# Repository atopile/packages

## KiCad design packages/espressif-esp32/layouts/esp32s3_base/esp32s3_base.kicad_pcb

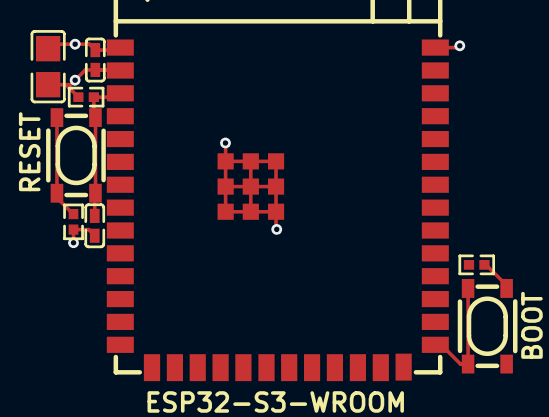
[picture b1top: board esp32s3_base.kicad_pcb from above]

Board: 2 copper layers, 9 parts (0 on the bottom side), 6 nets.

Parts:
C1: 100nF ±10% 16V X7R; C0402
C2: 22µF ±20% 25V X5R; C0805
C3: 1µF ±10% 25V X5R; C0402
R1, R3: 100Ω ±1% 62.5mW; R0402
R2: 10kΩ ±1% 62.5mW; R0402
SW1, SW2: KEY-SMD_4P-L4.2-W3.2-P2.20-LS4.6
U1: WIRELM-SMD_ESP32-S3-WROOM-1

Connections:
EN: C3.1, R2.1, SW2.1, SW2.2, U1.3
gnd: C1.2, C2.2, C3.2, R1.2, R3.2, U1.1, U1.40, U1.41
hv: C1.1, C2.1, R2.2, U1.2
line: SW1.1, SW1.2, U1.27
unnamed[1]: R3.1, SW2.3, SW2.4
unnamed[1]-1: R1.1, SW1.3, SW1.4

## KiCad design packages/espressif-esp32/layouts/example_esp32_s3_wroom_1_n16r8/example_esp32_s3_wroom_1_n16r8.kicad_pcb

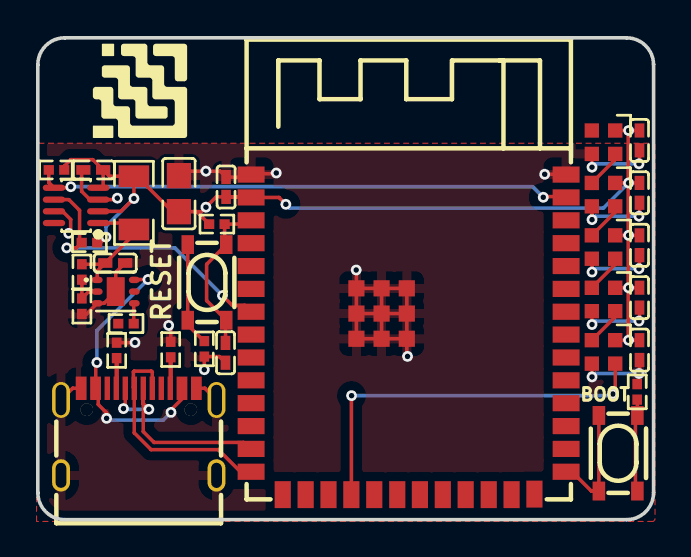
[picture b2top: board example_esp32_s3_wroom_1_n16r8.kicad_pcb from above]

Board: 2 copper layers, 34.2 x 26.8 mm, 32 parts (0 on the bottom side), 21 nets.

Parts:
C1, C2, C3, C4, C6, C7, C8: 100nF ±10% 16V X7R; C0402
C5, C10: 1µF ±10% 25V X5R; C0402
C9: 22µF ±20% 25V X5R; C0805
LED1, LED2, LED3, LED4, LED5: LED-SMD_4P-L2.0-W2.0-BR
R1: 180mΩ ±5% 250mW; R1206
R2, R4: 100Ω ±1% 62.5mW; R0402
R3, R5, R7: 10kΩ ±1% 62.5mW; R0402
R6: 2kΩ ±1% 62.5mW; R0402
R8, R9, R10, R11: 4.7kΩ ±1% 62.5mW; R0402
SW1, SW2: KEY-SMD_4P-L4.2-W3.2-P2.20-LS4.6
U1: SOT-23-8_L2.9-W1.6-P0.65-LS2.8-BR
U2: WIRELM-SMD_ESP32-S3-WROOM-1
U3: WSON-6_L2.0-W2.0-P0.65-TL-EP
USB1: USB-C-SMD_KH-TYPE-C-16P

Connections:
A5: R10.1, USB1.A5
B5: R11.1, USB1.B5
DIN: LED1.4, U2.18
DOUT: LED1.2, LED2.4
DOUT-1: LED2.2, LED3.4
DOUT-2: LED3.2, LED4.4
DOUT-3: LED4.2, LED5.4
EN: C10.1, R3.1, SW2.1, SW2.2, U2.3
FB: R6.1, R7.2, U3.2
IN: U3.6, USB1.A4, USB1.A9, USB1.B4, USB1.B9
SCL: R9.1, U1.5, U2.39
SDA: R8.1, U1.6, U2.7
gnd: C1.2, C2.2, C3.2, C4.2, C5.2, C6.2, C7.2, C8.2, C9.2, C10.2, LED1.3, LED2.3, LED3.3, LED4.3, LED5.3, R2.2, R4.2, R6.2, R10.2, R11.2, U1.3, U1.7, U2.1, U2.40, U2.41, U3.3, U3.7, USB1.1, USB1.2, USB1.3, USB1.4, USB1.A1, USB1.A12, USB1.B1, USB1.B12
hv: C1.1, C2.1, C3.1, C4.1, C6.1, C7.1, C8.1, C9.1, LED1.1, LED2.1, LED3.1, LED4.1, LED5.1, R1.2, R3.2, R8.2, R9.2, U1.2, U1.4, U2.2
hv-1: C5.1, R1.1, R7.1, U1.1, U3.1
ldo_3V3-EN: R5.2, U3.4
line: SW1.1, SW1.2, U2.27
line-1: U2.13, USB1.A7, USB1.B7
line-2: U2.14, USB1.A6, USB1.B6
unnamed[1]: R2.1, SW1.3, SW1.4
unnamed[1]-1: R4.1, SW2.3, SW2.4

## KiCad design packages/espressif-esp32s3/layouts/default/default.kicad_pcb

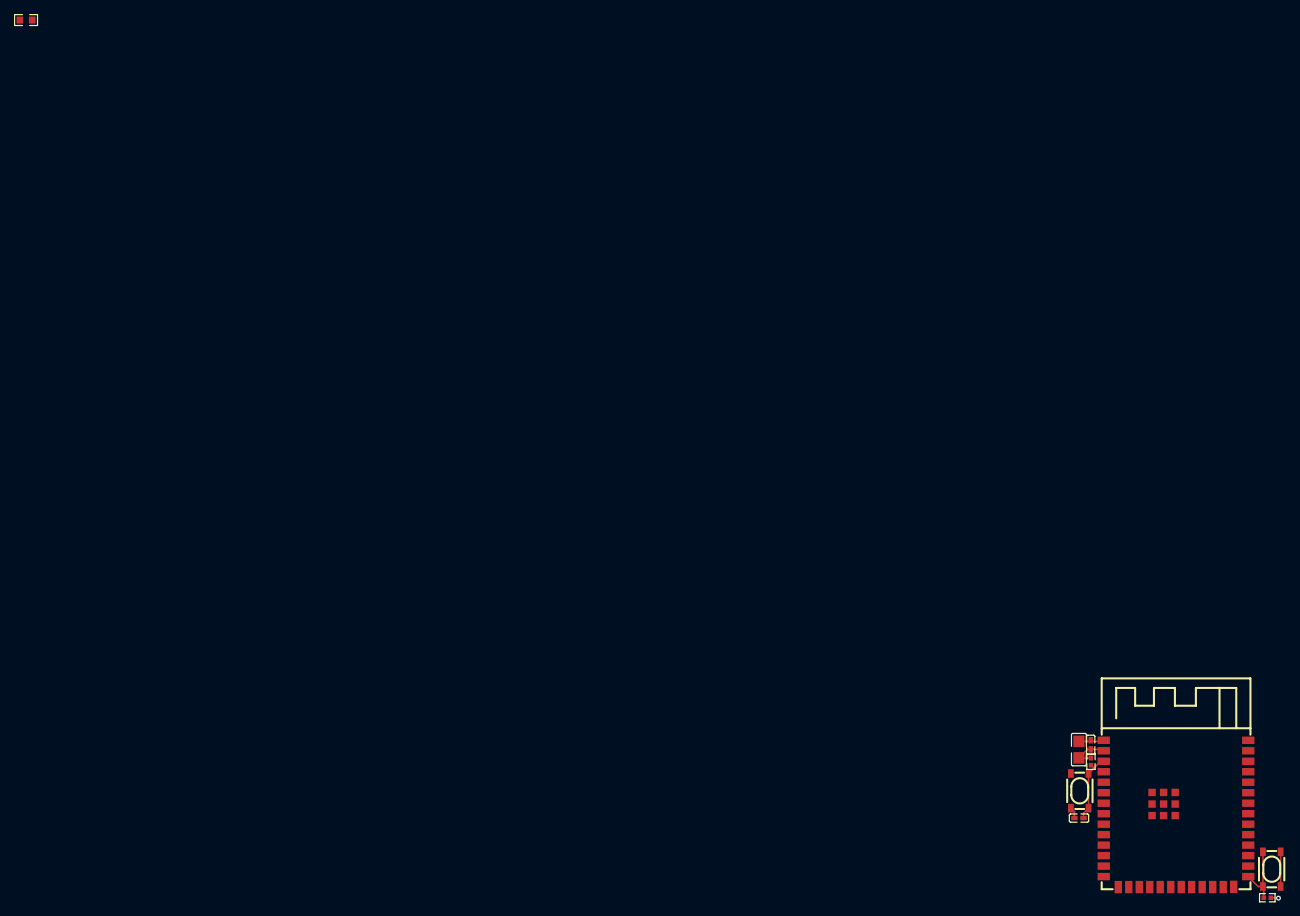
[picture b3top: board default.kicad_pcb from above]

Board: 2 copper layers, 9 parts (0 on the bottom side), 4 nets.

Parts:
C1: 10µF ±10% 25V X5R; C0805
C2: 100nF ±10% 16V X7R; C0402
C3: 1µF ±10% 25V X5R; C0402
R1, R2: 10kΩ ±1% 62.5mW; R0402
R3: 10kΩ ±1% 100mW; R0603
SW1, SW2: KEY-SMD_4P-L4.2-W3.2-P2.20-LS4.6
U1: WIRELM-SMD_ESP32-S3-WROOM-1

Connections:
GND: C1.2, C2.2, C3.2, SW1.1, SW1.2, SW2.1, SW2.2, U1.1, U1.40, U1.41
VCC: C1.1, C2.1, R1.1, R2.1, U1.2
enable-output: C3.1, R2.2, SW2.3, SW2.4, U1.3
io[0]-output: R1.2, SW1.3, SW1.4, U1.27

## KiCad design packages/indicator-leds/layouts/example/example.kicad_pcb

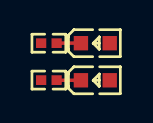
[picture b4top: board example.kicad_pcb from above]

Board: 2 copper layers, 4 parts (0 on the bottom side), 2 nets.

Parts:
LED1, LED2: LED0603-RD
R1: 10kΩ ±1% 62.5mW; R0402
R2: 1kΩ ±1% 62.5mW; R0402

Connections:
cathode-0: LED1.1, R1.1
cathode-1: LED2.1, R2.1
